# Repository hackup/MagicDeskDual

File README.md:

# MagicDeskCart Dual

The MagicDeskCart Dual is a bank switching cartridge for the C64/C128. In reminiscence of the "Double-Ender" cartridges that were produced for the Atari 2600, the MagicDeskCart Dual allows two different sets of banks to be selected by turning the cartridge around.

There is also no warranty whatsoever. **USE AT YOUR OWN RISK!**.

See my [blog post](https://www.hackup.net/2019/07/bank-switching-cartridges/) for more details.

## License
[
](http://creativecommons.org/licenses/by-nc-sa/4.0/)

This work is licensed under a
[Creative Commons Attribution-NonCommercial-ShareAlike 4.0 International License](http://creativecommons.org/licenses/by-nc-sa/4.0/).

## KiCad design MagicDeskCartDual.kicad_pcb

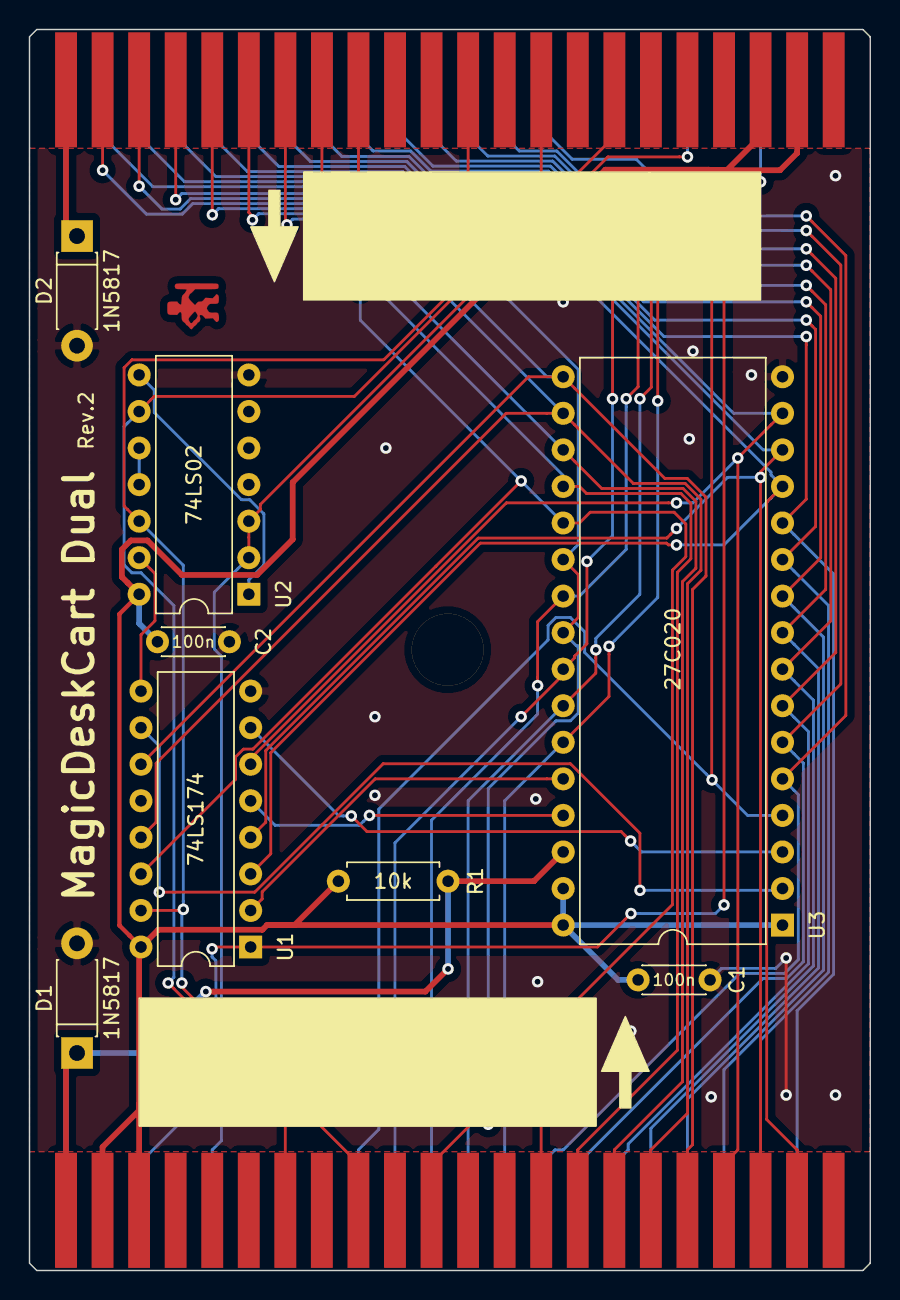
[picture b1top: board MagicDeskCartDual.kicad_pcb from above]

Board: 2 copper layers, 58.4 x 86.2 mm, 10 parts (0 on the bottom side), 37 nets.

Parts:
C1, C2: 100n; C_Disc_D4.3mm_W1.9mm_P5.00mm
D1, D2: 1N5817; D_DO-41_SOD81_P7.62mm_Horizontal
R1: 10k; R_Axial_DIN0207_L6.3mm_D2.5mm_P7.62mm_Horizontal
U1: 74LS174; DIP-16_W7.62mm
U2: 74LS02; DIP-14_W7.62mm
U3: 27C020; DIP-32_W15.24mm
U4, U5: C64-Exp-Port; C64-Cart-NoSilkS

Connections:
+5V: C1.1, C2.1, R1.1, U1.16, U2.14, U3.1, U3.31, U3.32, U4.2, U4.3, U5.2, U5.3
/A0: U3.12, U4.Y, U5.Y
/A1: U3.11, U4.X, U5.X
/A2: U3.10, U4.W, U5.W
/A3: U3.9, U4.V, U5.V
/A4: U3.8, U4.U, U5.U
/A5: U3.7, U4.T, U5.T
/A6: U3.6, U4.S, U5.S
/A7: U3.5, U4.R, U5.R
/A8: U3.27, U4.P, U5.P
/A9: U3.26, U4.N, U5.N
/A10: U3.23, U4.M, U5.M
/A11: U3.25, U4.L, U5.L
/A12: U3.4, U4.K, U5.K
/D0: U1.3, U3.13, U4.21, U5.21
/D1: U1.4, U3.14, U4.20, U5.20
/D2: U1.6, U3.15, U4.19, U5.19
/D3: U1.11, U3.17, U4.18, U5.18
/D4: U1.13, U3.18, U4.17, U5.17
/D5: U3.19, U4.16, U5.16
/D6: U3.20, U4.15, U5.15
/D7: U1.14, U3.21, U4.14, U5.14
/EN: U1.9, U2.13
/S13: U1.2, U3.28
/S14: U1.5, U3.29
/S15: U1.7, U3.3
/S16: U1.10, U3.2
EXROM: U1.15, U2.12, U4.9, U5.9
GND: C1.2, C2.2, D1.2, D2.2, U1.8, U2.7, U3.16
GND0: D1.1, R1.2, U3.30, U4.1, U4.A
GND1: D2.1, U5.22, U5.Z
IO1: U2.9, U4.7, U5.7
unnamed: U2.1, U2.8
unnamed: U2.10, U2.11
PHI2: U2.2, U2.3, U4.E, U5.E
RESET: U1.1, U4.C, U5.C
ROML: U3.22, U3.24, U4.11, U5.11

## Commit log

2019-06-17 Initial import.
2019-06-17 Tuning layout.
2019-06-18 Prepare for rev.1
2019-07-08 Moved traces away from the board edge.
2019-07-09 Added readme.
2019-07-11 Updated readme.
